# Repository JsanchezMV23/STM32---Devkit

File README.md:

# STM32 - Devkit with USB Connection + RGB Led

**STM32 based breakboard/devkit with USB connection and RGB Led with multiple pinout for ESP32 prototyping/code testing from scratch.** This small board has multiple connection for almost all GPIOs on the STM32F1 with a RGB led for simple code testing, a jumper for Booting and USB power/data connection.

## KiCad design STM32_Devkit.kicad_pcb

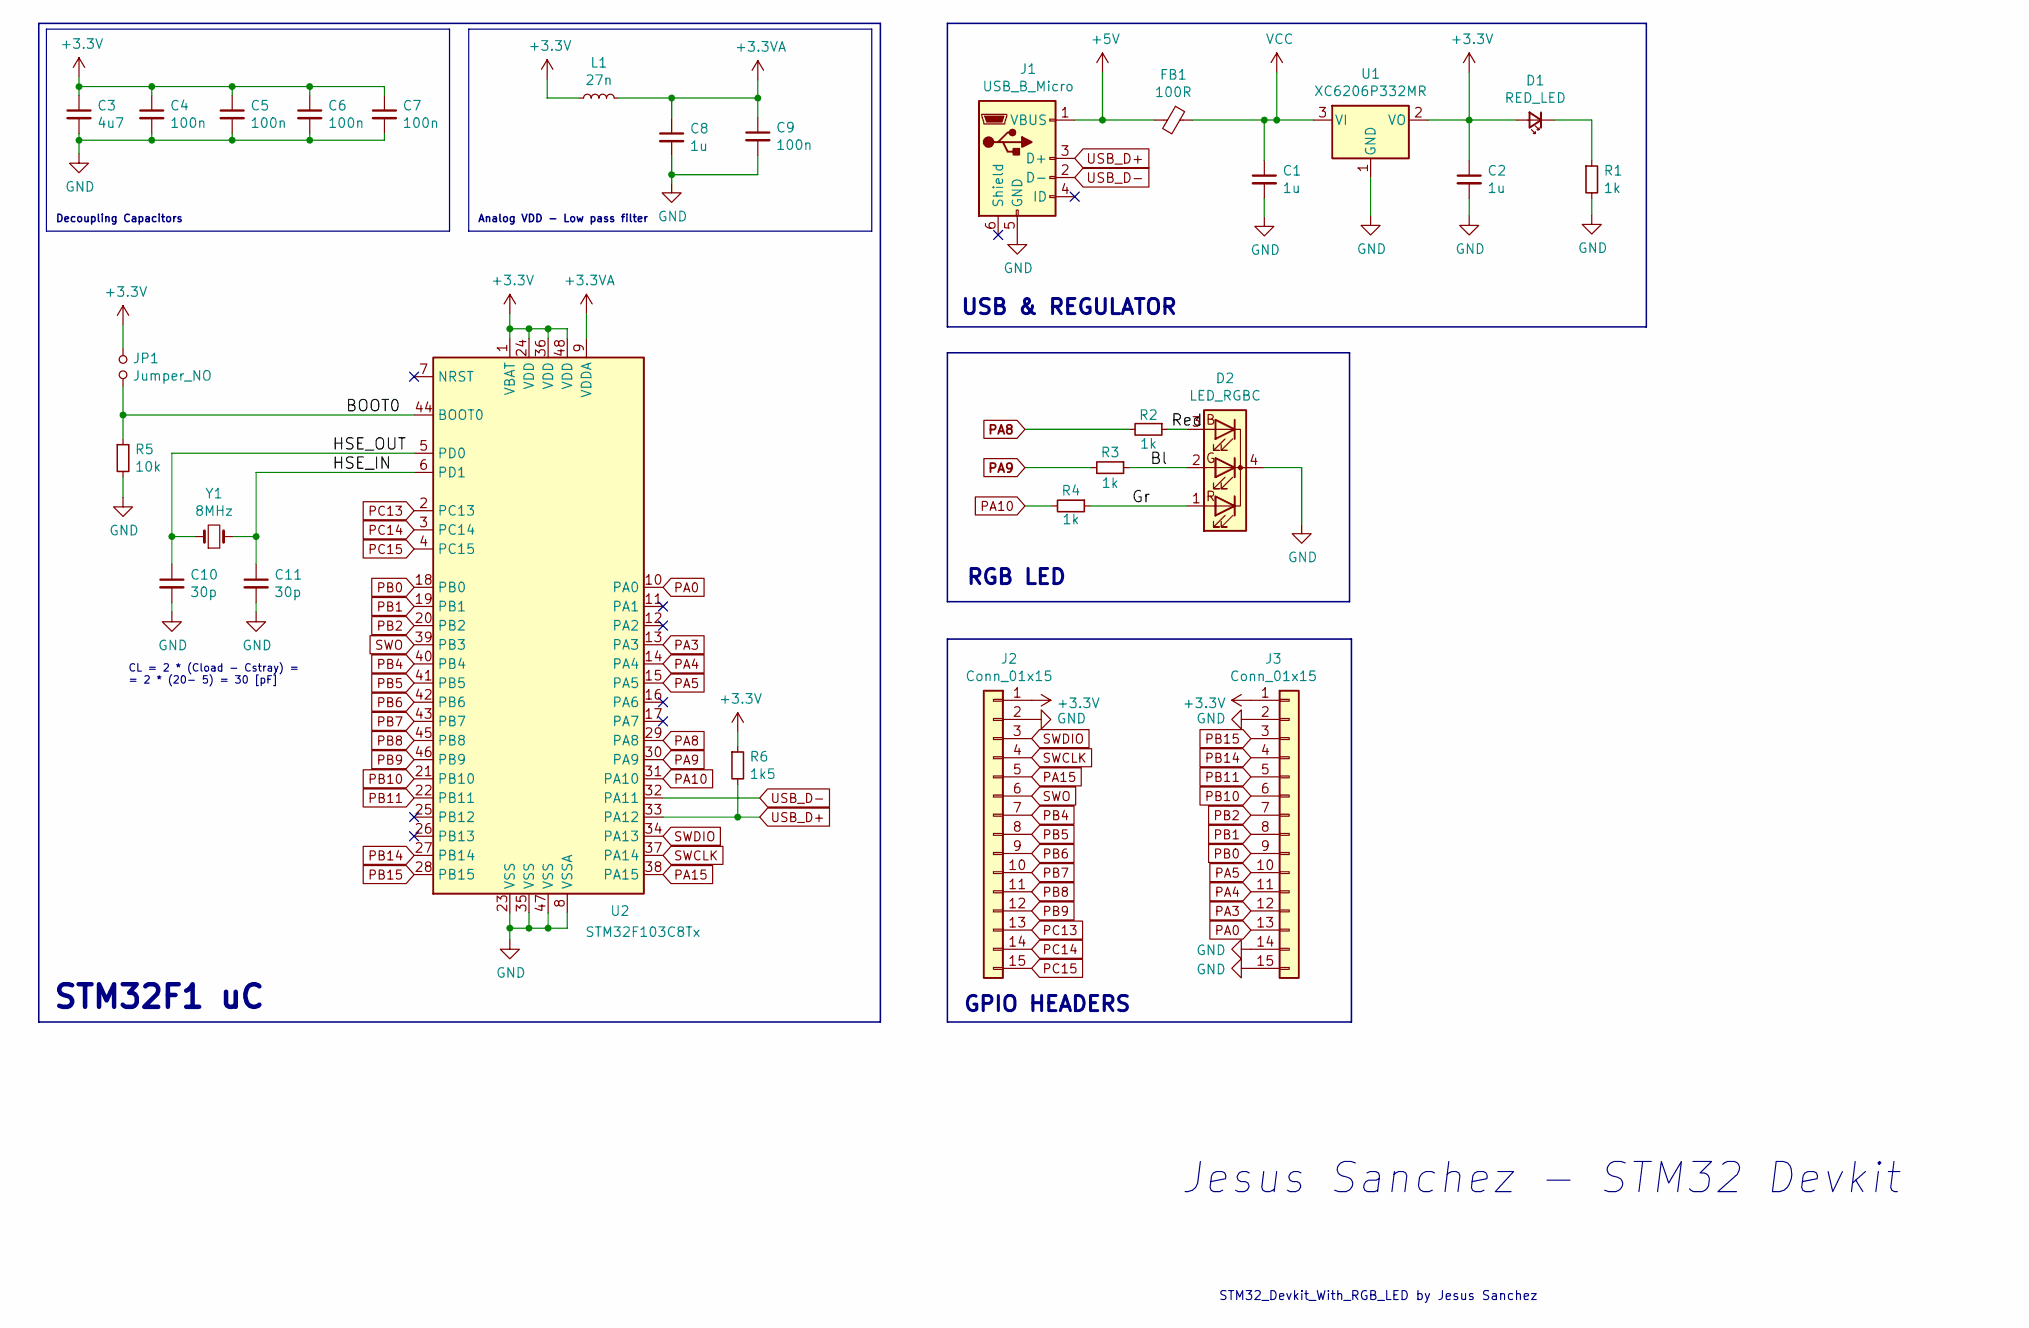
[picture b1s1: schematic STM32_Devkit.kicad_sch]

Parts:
C1, C2: 1u; C_0603_1608Metric
C3: 4u7; C_0603_1608Metric
C4, C5, C6, C7, C9: 100n; C_0402_1005Metric
C8: 1u; C_0402_1005Metric
C10, C11: 30p; C_0402_1005Metric
D1: RED_LED; LED_0603_1608Metric
D2: LED_RGBC; RGB_LED_2.1x2.1mm
FB1: 100R; L_0805_2012Metric
J1: USB_B_Micro; USB_Micro-B_Wuerth_629105150521
J2, J3: Conn_01x15; PinHeader_1x15_P2.54mm_Vertical
JP1: Jumper_NO; PinHeader_1x02_P2.54mm_Vertical
L1: 27n; L_0402_1005Metric
R1, R2, R3, R4: 1k; R_0603_1608Metric
R5: 10k; R_0603_1608Metric
R6: 1k5; R_0402_1005Metric
U1: XC6206P332MR; SOT-23
U2: STM32F103C8Tx; LQFP-48_7x7mm_P0.5mm
Y1: 8MHz; Crystal_SMD_5032-2Pin_5.0x3.2mm

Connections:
+3.3VA: C8.1, C9.1, L1.2, U2.9 (VDDA)
+3V3: C2.1, C3.1, C4.1, C5.1, C6.1, C7.1, D1.2 (A), J2.1, J3.1, JP1.1, L1.1, R6.1, U1.2 (VO), U2.1 (VBAT), U2.24 (VDD), U2.36 (VDD), U2.48 (VDD)
+5V: FB1.2, J1.1 (VBUS)
/BOOT0: JP1.2, R5.1, U2.44 (BOOT0)
/Bl: D2.2 (GA), R3.1
/Gr: D2.1 (RA), R4.1
/HSE_IN: C11.1, U2.6 (PD1), Y1.2
/HSE_OUT: C10.1, U2.5 (PD0), Y1.1
/Red: D2.3 (BA), R2.1
GND: C1.2, C2.2, C3.2, C4.2, C5.2, C6.2, C7.2, C8.2, C9.2, C10.2, C11.2, D2.4 (K), J1.5 (GND), J2.2, J3.2, J3.14, J3.15, R1.2, R5.2, U1.1 (GND), U2.8 (VSSA), U2.23 (VSS), U2.35 (VSS), U2.47 (VSS)
unnamed: D1.1 (K), R1.1
PA0: J3.13, U2.10 (PA0)
PA3: J3.12, U2.13 (PA3)
PA4: J3.11, U2.14 (PA4)
PA5: J3.10, U2.15 (PA5)
PA8: R2.2, U2.29 (PA8)
PA9: R3.2, U2.30 (PA9)
PA10: R4.2, U2.31 (PA10)
PA15: J2.5, U2.38 (PA15)
PB0: J3.9, U2.18 (PB0)
PB1: J3.8, U2.19 (PB1)
PB2: J3.7, U2.20 (PB2)
PB4: J2.7, U2.40 (PB4)
PB5: J2.8, U2.41 (PB5)
PB6: J2.9, U2.42 (PB6)
PB7: J2.10, U2.43 (PB7)
PB8: J2.11, U2.45 (PB8)
PB9: J2.12, U2.46 (PB9)
PB10: J3.6, U2.21 (PB10)
PB11: J3.5, U2.22 (PB11)
PB14: J3.4, U2.27 (PB14)
PB15: J3.3, U2.28 (PB15)
PC13: J2.13, U2.2 (PC13)
PC14: J2.14, U2.3 (PC14)
PC15: J2.15, U2.4 (PC15)
SWCLK: J2.4, U2.37 (PA14)
SWDIO: J2.3, U2.34 (PA13)
SWO: J2.6, U2.39 (PB3)
USB_D+: J1.3 (D+), R6.2, U2.33 (PA12)
USB_D-: J1.2 (D-), U2.32 (PA11)
VCC: C1.1, FB1.1, U1.3 (VI)

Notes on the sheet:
Decoupling Capacitors
CL = 2 * (Cload - Cstray) = = 2 * (20- 5) = 30 [pF]
GPIO HEADERS
STM32_Devkit_With_RGB_LED by Jesus Sanchez
USB & REGULATOR
RGB LED
Jesus Sanchez - STM32 Devkit
Analog VDD - Low pass filter
STM32F1 uC

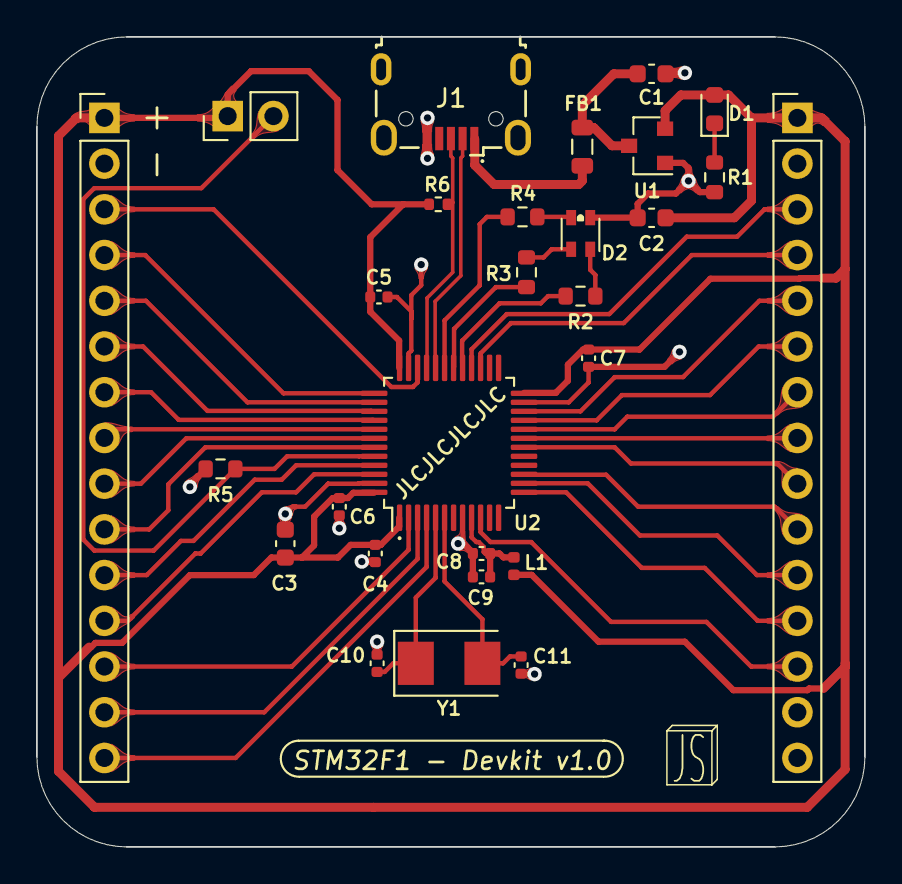
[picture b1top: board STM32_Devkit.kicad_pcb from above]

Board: 2 copper layers, 46.0 x 45.0 mm, 28 parts (0 on the bottom side), 41 nets.

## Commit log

2022-01-04 Create c
2022-01-05 Create d
